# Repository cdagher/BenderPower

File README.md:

# Bender ARS Power Supply

This repo serves as the home for power supply designs for the Bender Autonomous Robotic Systems (ARS) project at Boise State University. It contains hardware source files including schematics and PCB layout, as well as all firmware source files.

This source is provided as is, with no warranty whatsoever. Feel free to use it in your own projects, so long as you follow the [licensing terms](LICENSE).

## Hardware

We wanted our hardware to be flexible, as requirements can change from year to year depending on the goals of our team, design of the robot, and the competition we are targeting. As a result of this, we determined that our power supply should be *modular*. I don't mean modular like a modular ATX power supply, I mean that we can put in almost any power source, and get almost any supply voltages and currents on the output. This is obviously a tall order, so we settled for an input voltage of 0~60 VDC, a switching capacity of 55 A, and having three replaceable power modules. These modules should be cold-swappable, and can be designed to output nearly any voltage and current within a set power budget. As a final piece, we gave the board three hot-swappable power inputs so that we can power it from multiple batteries or power supplies simultaneously if we want to.

Currently, our power supply is split into three parts as follows:

1. A switching board which handles up to three inputs which are digitally fused to handle things like over-current, under- and over-voltage conditions, brown-outs, over-temperature conditions. Just to name a few. There are also three slots for our replaceable power modules, and one bank of output terminals for motor drivers directly from the input voltage.

2. A series of power modules which fit into a "standard" socket. We made a standard for ourselves from off the shelf connectors such that the modules will sit flush with the switching board, in case we need to give them a heatsink.

3. A controller. Our digital fuses on the inputs and power modules communicate over PMBus, so we need a way of controlling and coordinating everything. As long as the controller fits the bolt pattern and shape specified, it will easily bolt on to the top of the switching board and connect to everything with a wire harness. The decision to break this out into a separate board also simplified design and routing on the switching baord, and allowed for it to be designed for a cheaper 2-layer manufacturing process.

Renderings of the various boards can be seen below.

**Switching Board**

Top view of the switching board

Bottom view of the switching board

**Power Module Examples**

TODO

**Controller**

Top view of the controller PCB

Bottom View of the controller PCB

Side view of the controller PCB

## Firmware
TODO

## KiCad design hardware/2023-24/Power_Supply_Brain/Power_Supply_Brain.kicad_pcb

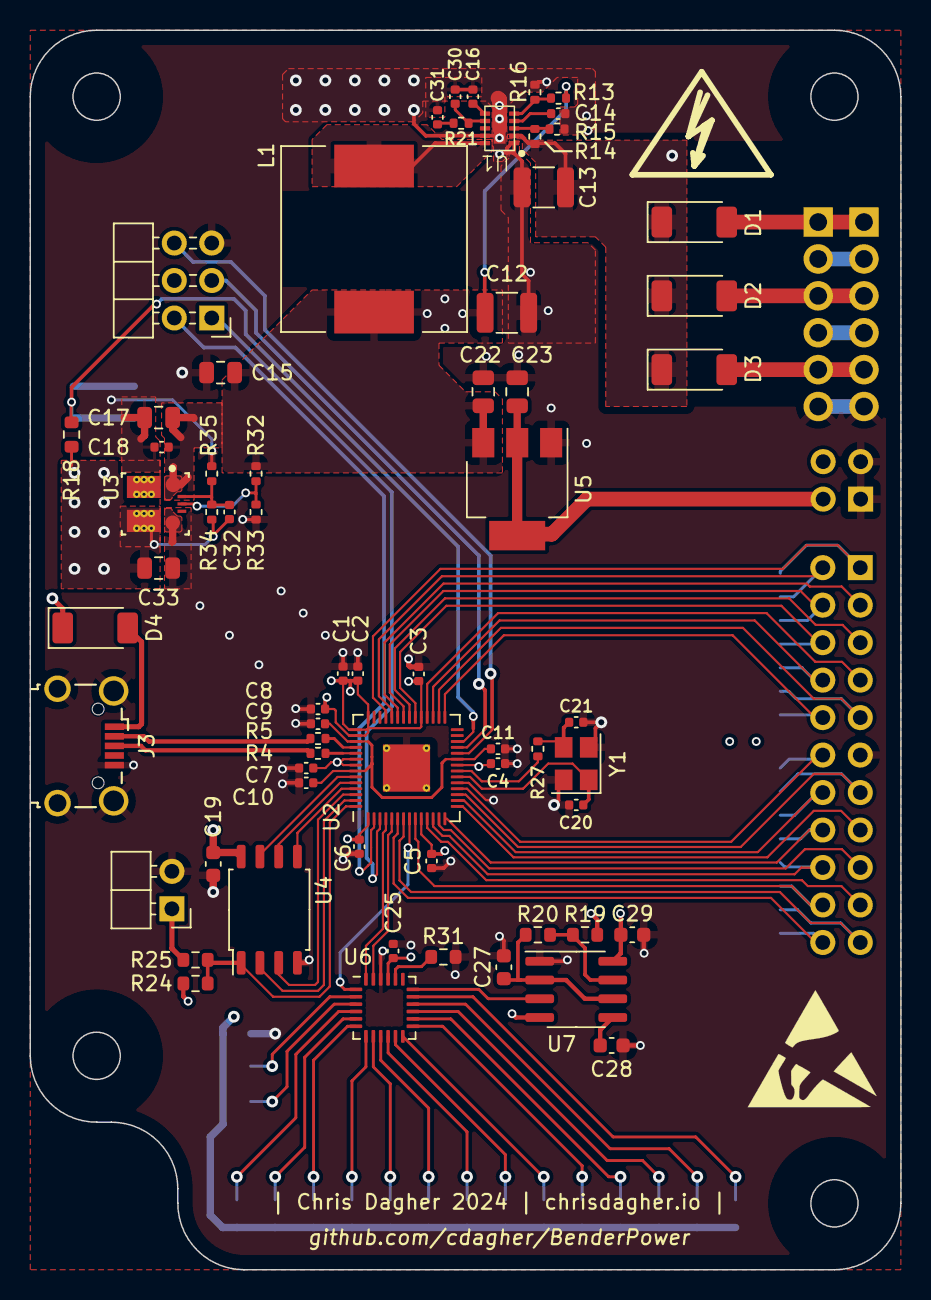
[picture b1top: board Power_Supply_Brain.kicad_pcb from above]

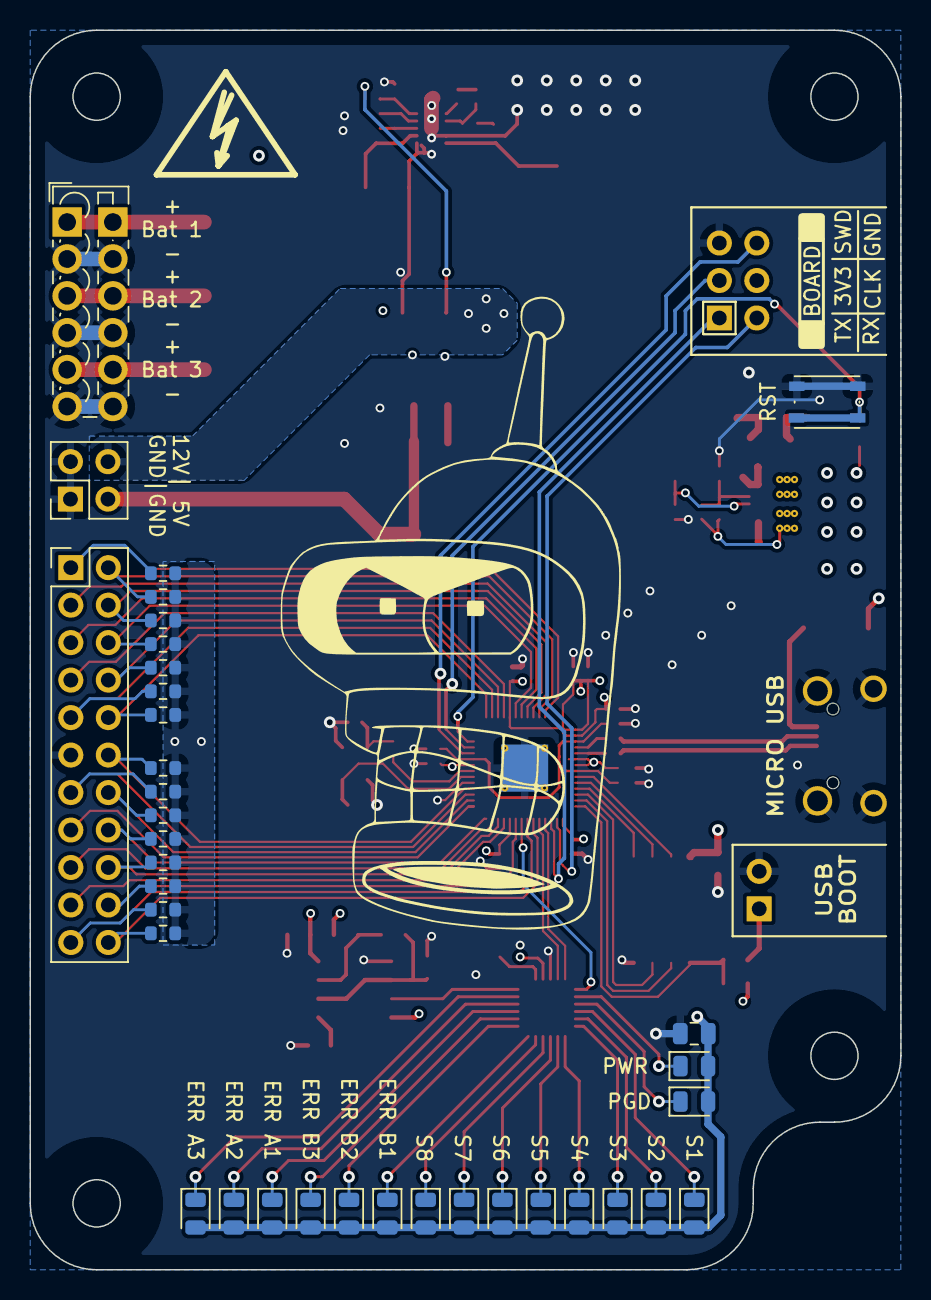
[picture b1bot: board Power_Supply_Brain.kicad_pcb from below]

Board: 4 copper layers, 59.0 x 84.0 mm, 101 parts (36 on the bottom side), 83 nets.

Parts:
C1, C2, C3, C4, C5, C6, C7, C10, C11, C18: 100n; C_0402_1005Metric
C8, C9, C14, C25: 1u; C_0402_1005Metric
C12: 10u; C_1210_3225Metric
C13: 2.2u; C_1210_3225Metric
C15, C17, C22, C23: 10u; C_0805_2012Metric
C16: 6800p; C_0402_1005Metric
C19: 100n; C_0603_1608Metric
C20, C21: 15p; C_0402_1005Metric
C26: 47u; C_0805_2012Metric
C27: 600p; C_0603_1608Metric
C28: DNP; C_0603_1608Metric
C29: 1u; C_0603_1608Metric
C30: 12p; C_0402_1005Metric
C31: 2200p; C_0402_1005Metric
C32: 22p; C_0402_1005Metric
C33: 22u; C_0805_2012Metric
D1, D2, D3, D4: PMEG10030ELPX; D_SOD-128
D5, D6, D7, D8, D9, D10, D11, D12, D13, D14, D15, D16, D17, D18, D19, D20: LED; LED_0805_2012Metric
J1: Conn_02x03_Odd_Even; PinHeader_2x03_P2.54mm_Horizontal
J2: Conn_02x02_Counter_Clockwise; PinHeader_2x02_P2.54mm_Vertical
J3: USB_B_Micro; USB_Micro-B_Wuerth_629105150521_CircularHoles
J4: Conn_01x02; PinHeader_1x02_P2.54mm_Horizontal
J5: Screw_Terminal_01x06; TerminalBlock_Phoenix_PTSM-0,5-6-2.5-V-THR_1x06_P2.50mm_Ver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
J6: Conn_02x11_Counter_Clockwise; PinHeader_2x11_P2.54mm_Vertical
L1: 47u; L_12x12mm_H6mm
R1, R2, R3, R6, R8, R9, R10, R11, R12, R18: 10k; R_0603_1608Metric
R4, R5: 27.4; R_0402_1005Metric
R7, R17, R22, R23, R26, R28: 100k; R_0603_1608Metric
R13: 174k; R_0402_1005Metric
R14: 3.3M; R_0402_1005Metric
R15: 453k; R_0402_1005Metric
R16: 14k; R_0402_1005Metric
R19: 220; R_0603_1608Metric
R20: 1.1k; R_0603_1608Metric
R21: 20k; R_0402_1005Metric
R24: DNP; R_0603_1608Metric
R25: 1k; R_0603_1608Metric
R27: 1k; R_0402_1005Metric
R31: 11k; R_0603_1608Metric
R32: 62k; R_0402_1005Metric
R33, R35: 30k; R_0402_1005Metric
R34: 135k; R_0402_1005Metric
SW1: SW_MEC_5G; SW_Push_1P1T_NO_Vertical_Wuerth_434133025816
U1: MAX17502G; TDFN
U2: RP2040; QFN-56-1EP_7x7mm_P0.4mm_EP3.2x3.2mm_ThermalVias
U3: TPSM861252RDXR; RDX0007A-MFG
U4: W25Q128JVS; SOIC-8_5.23x5.23mm_P1.27mm
U5: NCP1117-5.0_SOT223; SOT-223-3_TabPin2
U6: LED1642GWQTR; QFN-24-1EP_4x4mm_P0.5mm_EP2.15x2.15mm
U7: LMC555xM; SOIC-8_3.9x4.9mm_P1.27mm
Y1: ABLS-12.000MHZ-B4-T; Crystal_SMD_Abracon_ABM8G-4Pin_3.2x2.5mm

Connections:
+1V1: C9.1, C10.1, C11.1, U2.23 (DVDD), U2.45 (VREG_VOUT), U2.50 (DVDD)
+3V3: C1.1, C2.1, C3.1, C4.1, C5.1, C6.1, C7.1, C8.1, C19.1, C25.1, C26.1, C29.1, C32.1, C33.1, D5.2 (A), D6.2 (A), D7.2 (A), D8.2 (A), D9.2 (A), D10.2 (A), D11.2 (A), D12.2 (A), D13.2 (A), D14.2 (A), D15.2 (A), D16.2 (A), D17.2 (A), D18.2 (A), D19.2 (A), D20.2 (A), J1.4, R1.1, R2.2, R3.2, R6.2, R7.2, R8.1, R9.1, R10.1, R11.1, R12.1, R17.2, R18.1, R19.1, R22.2, R23.2, R24.1, R26.2, R28.2, R34.1, U2.1 (IOVDD), U2.10 (IOVDD), U2.22 (IOVDD), U2.33 (IOVDD), U2.42 (IOVDD), U2.43 (ADC_AVDD), U2.44 (VREG_IN), U2.48 (USB_VDD), U2.49 (IOVDD), U3.3 (VOUT), U3.11, U3.12, U3.13, U3.17, U3.18, U3.19, U4.8 (VCC), U6.21 (VDD), U7.4 (R), U7.8 (VCC)
+5V: C23.1, J2.3, U5.2 (VO)
+9V: C12.2 (-), C15.1, C17.1, C18.1, C22.1, J2.4, L1.2, R13.1, R32.1, U3.1 (VIN), U5.3 (VI)
/+12V_LX: L1.1, U1.10 (LX)
/LED Matrix/PWCLK: U6.18 (PWCLK), U7.3 (Q)
/LED Matrix/THR/TR: C27.1, R20.2, U7.2 (TR), U7.6 (THR)
/MCU_REG_IN: C13.2 (-), D1.1 (K), D2.1 (K), D3.1 (K), D4.1 (K), R14.1, U1.2 (VIN)
/QSPI_SCLK: U2.52 (QSPI_SCLK), U4.6 (CLK)
/QSPI_SD0: U2.53 (QSPI_SD0), U4.5 (DI(IO0))
/QSPI_SD1: U2.55 (QSPI_SD1), U4.2 (DO(IO1))
/QSPI_SD2: U2.54 (QSPI_SD2), U4.3 (IO2)
/QSPI_SD3: U2.51 (QSPI_SD3), U4.7 (IO3)
/QSPI_SS: R24.2, R25.1, U2.56 (QSPI_SS), U4.1 (~CS)
/SWCLK: J1.6, U2.24 (SWCLK)
/SWD: J1.3, U2.25 (SWD)
/UART0_RX: J1.1, U2.3 (GPIO1)
/UART0_TX: J1.2, U2.2 (GPIO0)
/USB_D_N: J3.2 (D-), R5.1
/USB_D_P: J3.3 (D+), R4.1
/XIN: C20.1, U2.20 (XIN), Y1.1
/XOUT: R27.1, U2.21 (XOUT)
/~USB_BOOT: J4.1, R25.2
ADC1_RDY: J6.10, R2.1, U2.29 (GPIO18)
ADC2_RDY: J6.9, R3.1, U2.30 (GPIO19)
ALRT_B1: J6.14, R8.2, U2.16 (GPIO13)
ALRT_B2: J6.13, R9.2, U2.17 (GPIO14)
ALRT_B3: J6.12, R10.2, U2.18 (GPIO15)
EN_AUX_1: J6.7, U2.32 (GPIO21)
EN_AUX_2: J6.5, U2.35 (GPIO23)
EN_AUX_3: J6.3, U2.37 (GPIO25)
EN_B1: J6.15, U2.15 (GPIO12)
EN_B2: J6.17, U2.13 (GPIO10)
EN_B3: J6.19, U2.11 (GPIO8)
GND: C1.2, C2.2, C3.2, C4.2, C5.2, C6.2, C7.2, C8.2, C9.2, C10.2, C11.2, C12.1 (+), C13.1 (+), C14.1 (+), C15.2, C16.1 (+), C17.2, C18.2, C19.2, C20.2, C21.2, C22.2, C23.2, C25.2, C26.2, C27.2, C28.1, C29.2, C30.2, C31.2, C33.2, J1.5, J2.1, J2.2, J3.5 (GND), J3.6 (Shield), J4.2, J5.2, J5.4, J5.6, J6.11, R15.2, R16.2, R31.1, R33.2, R35.2, SW1.2 (A), U1.1 (PGND), U1.9 (GND), U2.19 (TESTEN), U2.57 (GND), U3.4 (PGND), U4.4 (GND), U5.1 (GND), U6.22 (GND), U7.1 (GND), Y1.2 (3), Y1.4
I2C0_SCL: J6.21, R11.2, U2.7 (GPIO5)
I2C0_SDA: J6.22, R12.2, U2.6 (GPIO4)
I2C1_SCL: J6.1, R6.1, U2.39 (GPIO27_ADC1)
I2C1_SDA: J6.2, R1.2, U2.38 (GPIO26_ADC0)
LED_CLK: U2.4 (GPIO2), U6.24 (CLK)
LED_EN: U2.8 (GPIO6), U6.1 (LE)
LED_SDI: U2.5 (GPIO3), U6.23 (SDI)
unnamed: C14.2 (-), U1.4 (VCC)
unnamed: C16.2 (-), U1.6 (SS)
unnamed: C21.1, R27.2, Y1.3
unnamed: C31.1, R21.2
unnamed: D4.2 (A), J3.1 (VBUS)
unnamed: D5.1 (K), U6.2 (OUT0)
unnamed: D6.1 (K), U6.3 (OUT1)
unnamed: D7.1 (K), U6.4 (OUT2)
unnamed: D8.1 (K), U6.5 (OUT3)
unnamed: D9.1 (K), U6.6 (OUT4)
unnamed: D10.1 (K), U6.7 (OUT5)
unnamed: D11.1 (K), U6.8 (OUT6)
unnamed: D12.1 (K), U6.9 (OUT7)
unnamed: D13.1 (K), U6.10 (OUT8)
unnamed: D14.1 (K), U6.11 (OUT9)
unnamed: D15.1 (K), U6.12 (OUT10)
unnamed: D16.1 (K), U6.13 (OUT11)
unnamed: D17.1 (K), U6.14 (OUT12)
unnamed: D18.1 (K), U6.15 (OUT13)
unnamed: D19.1 (K), U6.16 (OUT14)
unnamed: D20.1 (K), U6.17 (OUT15)
unnamed: R14.2, R15.1, U1.3 (EN/UVLO)
unnamed: R13.2, R16.1, U1.5 (FB/VO)
unnamed: C30.1, R21.1, U1.7 (NC/COMP)
unnamed: R18.2, SW1.1 (A), U2.26 (RUN)
unnamed: R5.2, U2.46 (USB_DM)
unnamed: R4.2, U2.47 (USB_DP)
unnamed: R32.2, R33.1, U3.6 (EN)
unnamed: C32.2, R34.2, R35.1, U3.7 (FB)
unnamed: R31.2, U6.20 (R-EXT)
unnamed: C28.2, U7.5 (CV)
unnamed: R19.2, R20.1, U7.7 (DIS)
PGD_AUX1: J6.8, R23.1, U2.31 (GPIO20)
PGD_AUX2: J6.6, R26.1, U2.34 (GPIO22)
PGD_AUX3: J6.4, R28.1, U2.36 (GPIO24)
PGD_B1: J6.16, R7.1, U2.14 (GPIO11)
PGD_B2: J6.18, R17.1, U2.12 (GPIO9)
PGD_B3: J6.20, R22.1, U2.9 (GPIO7)
VIN_B1: D1.2 (A), J5.1
VIN_B2: D2.2 (A), J5.3
VIN_B3: D3.2 (A), J5.5

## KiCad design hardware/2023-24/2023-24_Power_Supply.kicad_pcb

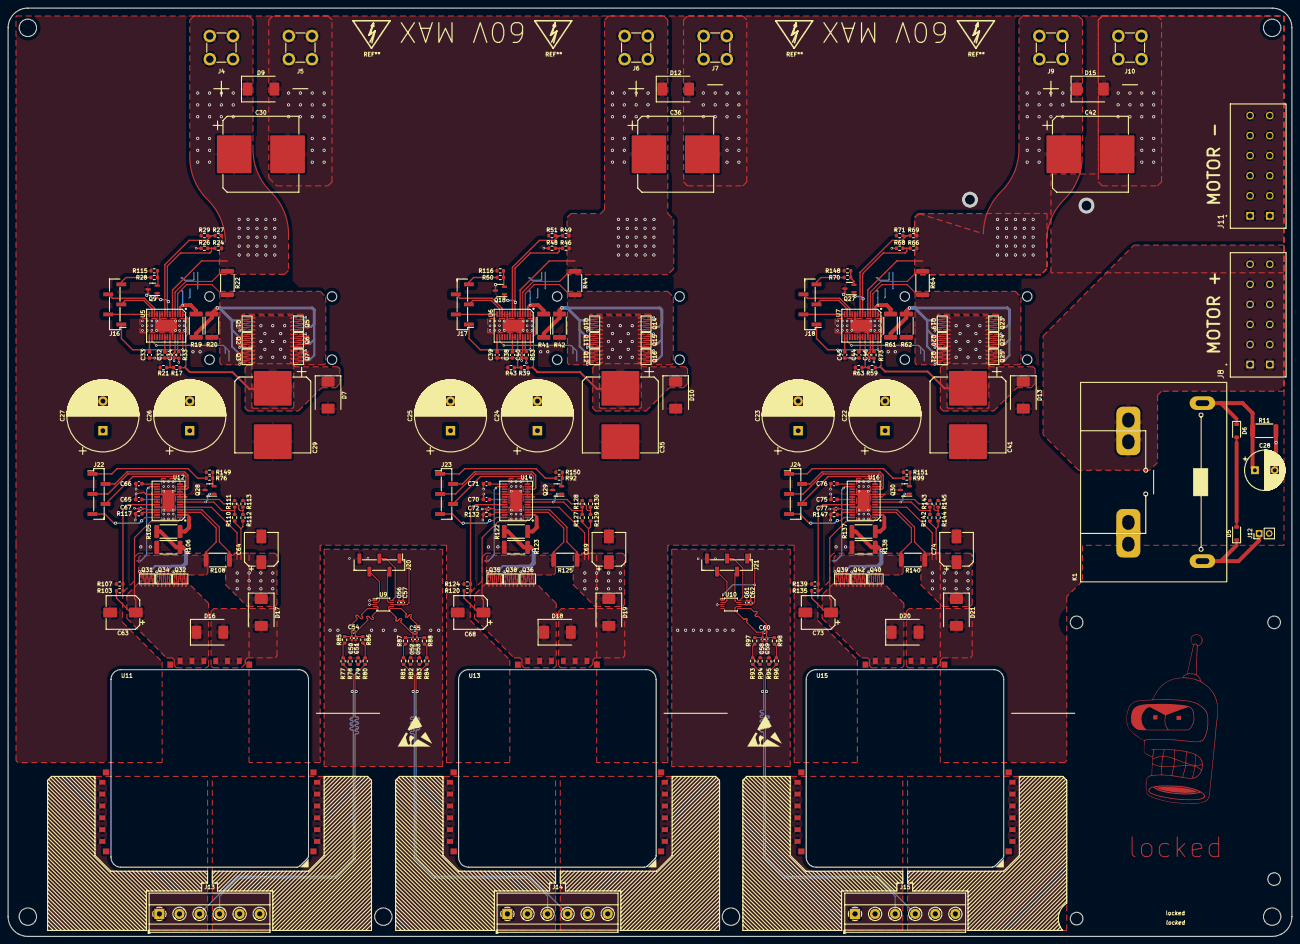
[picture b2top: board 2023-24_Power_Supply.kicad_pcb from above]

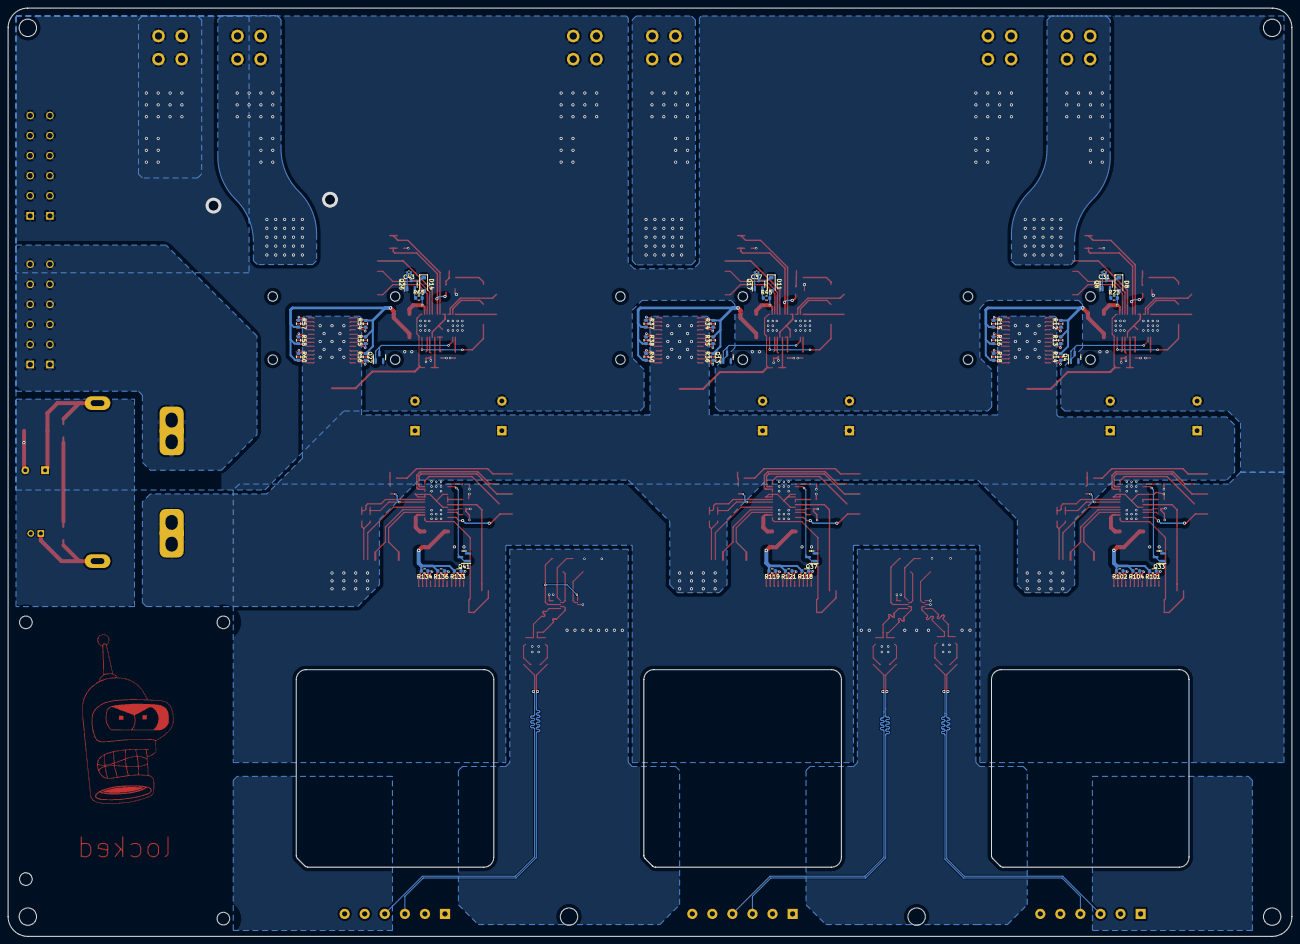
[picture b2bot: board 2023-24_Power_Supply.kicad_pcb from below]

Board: 2 copper layers, 325.0 x 235.0 mm, 265 parts (45 on the bottom side), 171 nets.

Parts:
C22, C23, C24, C25, C26, C27: 330u; CP_Radial_D18.0mm_P7.50mm
C28: 22u; CP_Radial_D10.0mm_P5.00mm
C29, C30, C35, C36, C41, C42: 220u; CP_Elec_18x17.5
C31, C37, C43: 30n; C_0402_1005Metric
C32, C33, C38, C39, C44, C45, C65, C66, C70, C71, C75, C76: 1u; C_0603_1608Metric
C34, C40, C46: 10n; C_0402_1005Metric
C50, C51, C52, C53, C58, C59: 50n; C_0402_1005Metric
C54, C55, C60: 5p; C_0402_1005Metric
C56, C61: 0.1u; C_0402_1005Metric
C57, C62: 1.0u; C_0402_1005Metric
C63, C64, C68, C69, C73, C74: 22u; CP_Elec_8x10
C67, C72, C77: 75n; C_0402_1005Metric
D5: 120V; D_SOD-123
D6: 36V; D_SOD-123
D7, D10, D13, D16, D18, D20: 80V; D_SMC
D8, D11, D14: 100V; D_SOD-123
D9, D12, D15, D17, D19, D21: 60V; D_SMC
J4, J5, J6, J7, J9, J10: Screw_Terminal_01x01; Wuerth_REDCUBE-THR_WP-THRSH_74651174_THR
J8, J11: TBL007A-508-06GY; CUI_TBL007A-508-06GY
J12: Conn_01x02; PinHeader_1x02_P2.54mm_Vertical
J13, J14, J15: Screw_Terminal_01x06; TerminalBlock_Phoenix_MKDS-1,5-6-5.08_1x06_P5.08mm_Horizont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
J16, J17, J18, J20, J21, J22, J23, J24: Conn_01x05_Pin; PinHeader_1x05_P2.54mm_Vertical_SMD_Pin1Left
K1: G9KB-1A-E DC12; Relay_SPST_Omron_G9KB
Q1, Q2, Q3, Q5, Q6, Q7, Q10, Q11, Q12, Q14, Q15, Q16, Q19, Q20, Q21, Q23, Q24, Q25, Q31, Q32, Q34, Q35, Q36, Q38, Q39, Q40, Q42: WLCSP-8
Q4, Q13, Q22, Q33, Q37, Q41: SOT-23
Q8, Q17, Q26: PNP; SOT-23-3
Q9, Q18, Q27, Q28, Q29, Q30: NMOS; SOT-23-3
R11: 68; R_2512_6332Metric
R12, R13, R14, R15, R16, R18, R34, R35, R36, R37, R38, R40, R54, R55, R56, R57, R58, R60: 180; R_0603_1608Metric
R17, R24, R39, R46, R59, R66, R77, R80, R81, R84, R93, R96, R103, R110, R120, R127, R135, R142: 100k; R_0603_1608Metric
R19, R41, R61, R105, R122, R137: 56; R_2512_6332Metric
R20, R42, R62, R106, R123, R138: 30; R_2512_6332Metric
R21, R43, R63, R107, R124, R139: 21.3k; R_0603_1608Metric
R22, R44, R64: 500u; R_2512_6332Metric
R23, R28, R45, R50, R65, R70, R76, R92, R99: 1k; R_0603_1608Metric
R26, R48, R68, R111, R128, R143: 33k; R_0603_1608Metric
R27, R49, R69, R112, R129, R144: 95k; R_0603_1608Metric
R29, R51, R71, R113, R130, R145: 3.9k; R_0603_1608Metric
R33, R53, R73: 45.3k; R_0603_1608Metric
R78, R79, R82, R83, R85, R86, R87, R88, R94, R95, R97, R98, R115, R116, R148, R149, R150, R151: 10k; R_0603_1608Metric
R101, R102, R104, R118, R119, R121, R133, R134, R136: 82.5; R_0603_1608Metric
R108, R125, R140: 1.5m; R_2512_6332Metric
R117, R132, R147: 28.2k; R_0603_1608Metric
U5, U6, U7, U12, U14, U16: LM5066; HTSSOP-28
U9, U10: ADS1015IDGS; TSSOP-10_3x3mm_P0.5mm
U11, U13, U15: 50x50_slot

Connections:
+5.5V: C56.1, C57.1, C61.1, C62.1, J20.1, J21.1, U9.8 (VDD), U10.1 (ADDR), U10.8 (VDD)
/Aux Outputs/Aux 1/DIODE: Q33.1 (B), Q33.3 (C), U12.16 (DIODE)
/Aux Outputs/Aux 1/GATE: R101.2, R102.2, R104.2, R105.2, R106.1
/Aux Outputs/Aux 1/GATE_OUT: R105.1, U12.2 (GATE)
/Aux Outputs/Aux 1/I2C_SCL: J22.3, U12.13 (SCLK)
/Aux Outputs/Aux 1/I2C_SDA: J22.2, U12.11 (SDAI), U12.12 (SDAO)
/Aux Outputs/Aux 1/REG_VIN: C63.1 (+), D16.1 (K), Q31.2 (S), Q32.2 (S), Q34.2 (S), R103.1, U11.1 (VIN_1), U11.2 (VIN_2), U11.3 (VIN_3), U12.1 (OUT)
/Aux Outputs/Aux 1/UVLO/EN: Q28.1 (G), R110.2, R111.2, U12.7 (UVLO/EN)
/Aux Outputs/Aux 1/VD: Q31.3 (D), Q32.3 (D), Q34.3 (D), R108.2, U12.3 (SENSE)
/Aux Outputs/Aux 1/VDD: C65.1 (+), U12.21 (VDD), U12.22 (CL)
/Aux Outputs/Aux 2/DIODE: Q37.1 (B), Q37.3 (C), U14.16 (DIODE)
/Aux Outputs/Aux 2/GATE: R118.2, R119.2, R121.2, R122.2, R123.1
/Aux Outputs/Aux 2/GATE_OUT: R122.1, U14.2 (GATE)
/Aux Outputs/Aux 2/I2C_SCL: J23.3, U14.13 (SCLK)
/Aux Outputs/Aux 2/I2C_SDA: J23.2, U14.11 (SDAI), U14.12 (SDAO)
/Aux Outputs/Aux 2/REG_VIN: C68.1 (+), D18.1 (K), Q35.2 (S), Q36.2 (S), Q38.2 (S), R120.1, U13.1 (VIN_1), U13.2 (VIN_2), U13.3 (VIN_3), U14.1 (OUT)
/Aux Outputs/Aux 2/UVLO/EN: Q29.1 (G), R127.2, R128.2, U14.7 (UVLO/EN)
/Aux Outputs/Aux 2/VD: Q35.3 (D), Q36.3 (D), Q38.3 (D), R125.2, U14.3 (SENSE)
/Aux Outputs/Aux 2/VDD: C70.1 (+), U14.21 (VDD), U14.22 (CL)
/Aux Outputs/Aux 3/DIODE: Q41.1 (B), Q41.3 (C), U16.16 (DIODE)
/Aux Outputs/Aux 3/GATE: R133.2, R134.2, R136.2, R137.2, R138.1
/Aux Outputs/Aux 3/GATE_OUT: R137.1, U16.2 (GATE)
/Aux Outputs/Aux 3/I2C_SCL: J24.3, U16.13 (SCLK)
/Aux Outputs/Aux 3/I2C_SDA: J24.2, U16.11 (SDAI), U16.12 (SDAO)
/Aux Outputs/Aux 3/REG_VIN: C73.1 (+), D20.1 (K), Q39.2 (S), Q40.2 (S), Q42.2 (S), R135.1, U15.1 (VIN_1), U15.2 (VIN_2), U15.3 (VIN_3), U16.1 (OUT)
/Aux Outputs/Aux 3/UVLO/EN: Q30.1 (G), R142.2, R143.2, U16.7 (UVLO/EN)
/Aux Outputs/Aux 3/VD: Q39.3 (D), Q40.3 (D), Q42.3 (D), R140.2, U16.3 (SENSE)
/Aux Outputs/Aux 3/VDD: C75.1 (+), U16.20 (ADR0), U16.21 (VDD), U16.22 (CL)
/Aux Outputs/VOUT_AUX1_+: J13.1, J13.2, J13.3, R77.1, U11.7 (VOUT_1), U11.8 (VOUT_2), U11.9 (VOUT_3), U11.10 (VOUT_4), U11.11 (VOUT_5), U11.12 (VOUT_6)
/Aux Outputs/VOUT_AUX1_-: J13.4, J13.5, J13.6, R80.2, U11.13 (PGND_1), U11.14 (PGND_2), U11.15 (PGND_3), U11.16 (PGND_4), U11.17 (PGND_5), U11.18 (PGND_6)
/Aux Outputs/VOUT_AUX2_+: J14.1, J14.2, J14.3, R81.1, U13.7 (VOUT_1), U13.8 (VOUT_2), U13.9 (VOUT_3), U13.10 (VOUT_4), U13.11 (VOUT_5), U13.12 (VOUT_6)
/Aux Outputs/VOUT_AUX2_-: J14.4, J14.5, J14.6, R84.2, U13.13 (PGND_1), U13.14 (PGND_2), U13.15 (PGND_3), U13.16 (PGND_4), U13.17 (PGND_5), U13.18 (PGND_6)
/Aux Outputs/VOUT_AUX3_+: J15.1, J15.2, J15.3, R93.1, U15.7 (VOUT_1), U15.8 (VOUT_2), U15.9 (VOUT_3), U15.10 (VOUT_4), U15.11 (VOUT_5), U15.12 (VOUT_6)
/Aux Outputs/VOUT_AUX3_-: J15.4, J15.5, J15.6, R96.2, U15.13 (PGND_1), U15.14 (PGND_2), U15.15 (PGND_3), U15.16 (PGND_4), U15.17 (PGND_5), U15.18 (PGND_6)
/Battery Switching/Battery 1/DIODE: Q4.1 (B), Q4.3 (C), U5.16 (DIODE)
/Battery Switching/Battery 1/GATE: R12.2, R13.2, R14.2, R15.2, R16.2, R18.2, R19.2, R20.1
/Battery Switching/Battery 1/GATE_OUT: D8.2 (A+), R19.1, R23.2, U5.2 (GATE)
/Battery Switching/Battery 1/I2C_SCL: J16.3, U5.13 (SCLK)
/Battery Switching/Battery 1/I2C_SDA: J16.4, U5.11 (SDAI), U5.12 (SDAO)
/Battery Switching/Battery 1/UVLO/EN: Q9.1 (G), R24.2, R26.2, U5.7 (UVLO/EN)
/Battery Switching/Battery 1/VD: Q1.3 (D), Q2.3 (D), Q3.3 (D), Q5.3 (D), Q6.3 (D), Q7.3 (D), R22.2, U5.3 (SENSE)
/Battery Switching/Battery 1/VDD: C32.1 (+), U5.21 (VDD), U5.22 (CL)
/Battery Switching/Battery 2/DIODE: Q13.1 (B), Q13.3 (C), U6.16 (DIODE)
/Battery Switching/Battery 2/GATE: R34.2, R35.2, R36.2, R37.2, R38.2, R40.2, R41.2, R42.1
/Battery Switching/Battery 2/GATE_OUT: D11.2 (A+), R41.1, R45.2, U6.2 (GATE)
/Battery Switching/Battery 2/I2C_SCL: J17.3, U6.13 (SCLK)
/Battery Switching/Battery 2/I2C_SDA: J17.4, U6.11 (SDAI), U6.12 (SDAO)
/Battery Switching/Battery 2/UVLO/EN: Q18.1 (G), R46.2, R48.2, U6.7 (UVLO/EN)
/Battery Switching/Battery 2/VD: Q10.3 (D), Q11.3 (D), Q12.3 (D), Q14.3 (D), Q15.3 (D), Q16.3 (D), R44.2, U6.3 (SENSE)
/Battery Switching/Battery 2/VDD: C38.1 (+), U6.21 (VDD), U6.22 (CL)
/Battery Switching/Battery 3/DIODE: Q22.1 (B), Q22.3 (C), U7.16 (DIODE)
/Battery Switching/Battery 3/GATE: R54.2, R55.2, R56.2, R57.2, R58.2, R60.2, R61.2, R62.1
/Battery Switching/Battery 3/GATE_OUT: D14.2 (A+), R61.1, R65.2, U7.2 (GATE)
/Battery Switching/Battery 3/I2C_SCL: J18.3, U7.13 (SCLK)
/Battery Switching/Battery 3/I2C_SDA: J18.4, U7.11 (SDAI), U7.12 (SDAO)
/Battery Switching/Battery 3/UVLO/EN: Q27.1 (G), R66.2, R68.2, U7.7 (UVLO/EN)
/Battery Switching/Battery 3/VD: Q19.3 (D), Q20.3 (D), Q21.3 (D), Q23.3 (D), Q24.3 (D), Q25.3 (D), R64.2, U7.3 (SENSE)
/Battery Switching/Battery 3/VDD: C44.1 (+), U7.20 (ADR0), U7.21 (VDD), U7.22 (CL)
ADC1_RDY: J20.4, U9.2 (ALERT/RDY)
ADC2_RDY: J21.4, U10.2 (ALERT/RDY)
ALRT_AUX1: J22.4, U12.14 (SMBA)
ALRT_AUX2: J23.4, U14.14 (SMBA)
ALRT_AUX3: J24.4, U16.14 (SMBA)
ALRT_B1: J16.2, U5.14 (SMBA)
ALRT_B2: J17.2, U6.14 (SMBA)
ALRT_B3: J18.2, U7.14 (SMBA)
EN_AUX_1: J22.1, R76.1
EN_AUX_2: J23.1, R92.1
EN_AUX_3: J24.1, R99.1
EN_B1: J16.5, R28.1
EN_B2: J17.5, R50.1
EN_B3: J18.5, R70.1
GND: C22.2 (-), C23.2 (-), C24.2 (-), C25.2 (-), C26.2 (-), C27.2 (-), C29.2 (-), C30.2 (-), C31.2 (-), C32.2 (-), C33.2 (-), C34.2 (-), C35.2 (-), C36.2 (-), C37.2 (-), C38.2 (-), C39.2 (-), C40.2 (-), C41.2 (-), C42.2 (-), C43.2 (-), C44.2 (-), C45.2 (-), C46.2 (-), C50.1, C51.1, C52.1, C53.1, C56.2, C57.2, C58.1, C59.1, C61.2, C62.2, C63.2 (-), C64.2 (-), C65.2 (-), C66.2 (-), C67.2 (-), C68.2 (-), C69.2 (-), C70.2 (-), C71.2 (-), C72.2 (-), C73.2 (-), C74.2 (-), C75.2 (-), C76.2 (-), C77.2 (-), D7.2 (A), D9.2 (A), D10.2 (A), D12.2 (A), D13.2 (A), D15.2 (A), D16.2 (A), D17.2 (A), D18.2 (A), D19.2 (A), D20.2 (A), D21.2 (A), J5.1, J7.1, J10.1, J11.1_A (1), J11.1_B (1__1), J11.2_A (2), J11.2_B (2__1), J11.3_A (3), J11.3_B (3__1), J11.4_A (4), J11.4_B (4__1), J11.5_A (5), J11.5_B (5__1), J11.6_A (6), J11.6_B (6__1), J20.5, J21.5, Q4.2 (E), Q8.1 (B), Q9.3 (D), Q13.2 (E), Q17.1 (B), Q18.3 (D), Q22.2 (E), Q26.1 (B), Q27.3 (D), Q28.3 (D), Q29.3 (D), Q30.3 (D), Q33.2 (E), Q37.2 (E), Q41.2 (E), R20.2, R21.2, R26.1, R29.1, R33.1, R42.2, R43.2, R48.1, R51.1, R53.1, R62.2, R63.2, R68.1, R71.1, R73.1, R78.2, R79.1, R82.2, R83.1, R94.2, R95.1, R106.2, R107.2, R111.1, R113.1, R115.2, R116.2, R117.1, R123.2, R124.2, R128.1, R130.1, R132.1, R138.2, R139.2, R143.1, R145.1, R147.1, R148.2, R149.2, R150.2, R151.2, U5.9 (AGND), U5.10 (GND), U5.24 (RETRY), U6.9 (AGND), U6.10 (GND), U6.20 (ADR0), U6.24 (RETRY), U7.9 (AGND), U7.10 (GND), U7.24 (RETRY), U9.1 (ADDR), U9.3 (GND), U10.3 (GND), U11.4 (GND_1), U11.5 (GND_2), U11.6 (GND_3), U12.9 (AGND), U12.10 (GND), U12.19 (ADR1), U12.24 (RETRY), U13.4 (GND_1), U13.5 (GND_2), U13.6 (GND_3), U14.9 (AGND), U14.10 (GND), U14.19 (ADR1), U14.20 (ADR0), U14.24 (RETRY), U15.4 (GND_1), U15.5 (GND_2), U15.6 (GND_3), U16.9 (AGND), U16.10 (GND), U16.19 (ADR1), U16.24 (RETRY)
GND2: C28.2, J12.2, R11.2
I2C1_SCL: J20.3, J21.3, U9.10 (SCL), U10.10 (SCL)
I2C1_SDA: J20.2, J21.2, U9.9 (SDA), U10.9 (SDA)
unnamed: C31.1 (+), D8.1 (K-), Q8.3 (C)
unnamed: C33.1 (+), U5.15 (VREF)
unnamed: C34.1 (+), U5.25 (TIMER)
unnamed: C37.1 (+), D11.1 (K-), Q17.3 (C)
unnamed: C39.1 (+), U6.15 (VREF)
unnamed: C40.1 (+), U6.25 (TIMER)
unnamed: C43.1 (+), D14.1 (K-), Q26.3 (C)
unnamed: C45.1 (+), U7.15 (VREF)
unnamed: C46.1 (+), U7.25 (TIMER)
unnamed: C66.1 (+), U12.15 (VREF)
unnamed: C67.1 (+), U12.25 (TIMER)
unnamed: C71.1 (+), U14.15 (VREF)
unnamed: C72.1 (+), U14.25 (TIMER)
unnamed: C76.1 (+), U16.15 (VREF)
unnamed: C77.1 (+), U16.25 (TIMER)
unnamed: D5.2 (A+), D6.2 (A)
unnamed: C28.1, D6.1 (K), K1.2 (COIL_2), R11.1
unnamed: Q1.1 (G), R12.1
unnamed: Q2.1 (G), R13.1
unnamed: Q3.1 (G), R14.1
unnamed: Q5.1 (G), R15.1
unnamed: Q6.1 (G), R16.1
unnamed: Q7.1 (G), R18.1
unnamed: Q8.2 (E), R23.1
unnamed: Q9.2 (S), R28.2, R115.1
unnamed: Q10.1 (G), R34.1
unnamed: Q11.1 (G), R35.1
unnamed: Q12.1 (G), R36.1
unnamed: Q14.1 (G), R37.1
unnamed: Q15.1 (G), R38.1
unnamed: Q16.1 (G), R40.1
unnamed: Q17.2 (E), R45.1
unnamed: Q18.2 (S), R50.2, R116.1
unnamed: Q19.1 (G), R54.1
unnamed: Q20.1 (G), R55.1
unnamed: Q21.1 (G), R56.1
unnamed: Q23.1 (G), R57.1
unnamed: Q24.1 (G), R58.1
unnamed: Q25.1 (G), R60.1
unnamed: Q26.2 (E), R65.1
unnamed: Q27.2 (S), R70.2, R148.1
unnamed: Q28.2 (S), R76.2, R149.1
unnamed: Q29.2 (S), R92.2, R150.1
unnamed: Q30.2 (S), R99.2, R151.1
unnamed: Q31.1 (G), R101.1
unnamed: Q32.1 (G), R102.1
unnamed: Q34.1 (G), R104.1
unnamed: Q35.1 (G), R118.1
unnamed: Q36.1 (G), R119.1
unnamed: Q38.1 (G), R121.1
unnamed: Q39.1 (G), R133.1
unnamed: Q40.1 (G), R134.1
unnamed: Q42.1 (G), R136.1
unnamed: R77.2, R78.1, R85.2
unnamed: R79.2, R80.1, R86.2
unnamed: R81.2, R82.1, R87.2
unnamed: R83.2, R84.1, R88.2
unnamed: R93.2, R94.1, R97.2
unnamed: R95.2, R96.1, R98.2
unnamed: R17.2, R21.1, U5.23 (FB)
unnamed: R27.1, R29.2, U5.8 (OVLO)
unnamed: R33.2, U5.26 (PWR)
unnamed: R39.2, R43.1, U6.23 (FB)
unnamed: R49.1, R51.2, U6.8 (OVLO)
unnamed: R53.2, U6.26 (PWR)
unnamed: R59.2, R63.1, U7.23 (FB)
unnamed: R69.1, R71.2, U7.8 (OVLO)
unnamed: R73.2, U7.26 (PWR)
unnamed: C51.2, C54.2, R86.1, U9.4 (AIN0)
unnamed: C50.2, C54.1, R85.1, U9.5 (AIN1)
unnamed: C53.2, C55.2, R88.1, U9.6 (AIN2)
unnamed: C52.2, C55.1, R87.1, U9.7 (AIN3)
unnamed: C59.2, C60.2, R98.1, U10.6 (AIN2)
unnamed: C58.2, C60.1, R97.1, U10.7 (AIN3)
unnamed: R103.2, R107.1, U12.23 (FB)
unnamed: R112.1, R113.2, U12.8 (OVLO)
unnamed: R117.2, U12.26 (PWR)
unnamed: R120.2, R124.1, U14.23 (FB)
unnamed: R129.1, R130.2, U14.8 (OVLO)
unnamed: R132.2, U14.26 (PWR)
unnamed: R135.2, R139.1, U16.23 (FB)
unnamed: R144.1, R145.2, U16.8 (OVLO)
unnamed: R147.2, U16.26 (PWR)
PGD_AUX1: J22.5, U12.28 (PGD)
PGD_AUX2: J23.5, U14.28 (PGD)
PGD_AUX3: J24.5, U16.28 (PGD)
PGD_B1: J16.1, U5.28 (PGD)
PGD_B2: J17.1, U6.28 (PGD)
PGD_B3: J18.1, U7.28 (PGD)
RELAY_EN: D5.1 (K-), J12.1, K1.1 (COIL_1)
VIN_B1: C30.1 (+), D9.1 (K), J4.1, R22.1, R24.1, R27.2, U5.4 (VIN_K), U5.5 (VIN)
VIN_B2: C36.1 (+), D12.1 (K), J6.1, R44.1, R46.1, R49.2, U6.4 (VIN_K), U6.5 (VIN)
VIN_B3: C42.1 (+), D15.1 (K), J9.1, R64.1, R66.1, R69.2, U7.4 (VIN_K), U7.5 (VIN)
V_MOT: J8.1_A (1), J8.1_B (1__1), J8.2_A (2), J8.2_B (2__1), J8.3_A (3), J8.3_B (3__1), J8.4_A (4), J8.4_B (4__1), J8.5_A (5), J8.5_B (5__1), J8.6_A (6), J8.6_B (6__1), K1.4 (CONTACT_2)
V_SYS: C22.1 (+), C23.1 (+), C24.1 (+), C25.1 (+), C26.1 (+), C27.1 (+), C29.1 (+), C35.1 (+), C41.1 (+), C64.1 (+), C69.1 (+), C74.1 (+), D7.1 (K), D10.1 (K), D13.1 (K), D17.1 (K), D19.1 (K), D21.1 (K), K1.3 (CONTACT_1), Q1.2 (S), Q2.2 (S), Q3.2 (S), Q5.2 (S), Q6.2 (S), Q7.2 (S), Q10.2 (S), Q11.2 (S), Q12.2 (S), Q14.2 (S), Q15.2 (S), Q16.2 (S), Q19.2 (S), Q20.2 (S), Q21.2 (S), Q23.2 (S), Q24.2 (S), Q25.2 (S), R17.1, R39.1, R59.1, R108.1, R110.1, R112.2, R125.1, R127.1, R129.2, R140.1, R142.1, R144.2, U5.1 (OUT), U6.1 (OUT), U7.1 (OUT), U12.4 (VIN_K), U12.5 (VIN), U14.4 (VIN_K), U14.5 (VIN), U16.4 (VIN_K), U16.5 (VIN)

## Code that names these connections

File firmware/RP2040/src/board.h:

// Board configuration for RP2040

#ifndef BOARD_H
#define BOARD_H

#include "pico/stdlib.h"
#include "hardware/gpio.h"

#define BOARD_BENDER_BRAIN

// General pin configurations
#define UART_0_TX 0
#define UART_0_PIN_MODE GPIO_FUNC_UART
#define UART_0_RX 1
#define UART_0_PIN_MODE GPIO_FUNC_UART

#define I2C0_SDA 4
#define I2C0_PIN_MODE GPIO_FUNC_I2C
#define I2C0_SCL 5
#define I2C0_PIN_MODE GPIO_FUNC_I2C

#define I2C1_SDA 26
#define I2C1_PIN_MODE GPIO_FUNC_I2C
#define I2C1_SCL 27
#define I2C1_PIN_MODE GPIO_FUNC_I2C

// LED Driver pins
/*
LED Deiver is the LED1642GW from ST Microelectronics https://www.st.com/resource/en/datasheet/led1642gw.pdf

Note that the SDO pin is not used in this configuration, so there is no feedback
from the LED driver to the RP2040.
*/
#define LED_CLK 2
#define LED_CLK_MODE GPIO_FUNC_SIO
#define LED_SDI 3
#define LED_SDI_MODE GPIO_FUNC_SIO
#define LED_LEN  6
#define LED_LEN_MODE GPIO_FUNC_SIO

/* Battery Inputs 
Batteries are controlled using LM5066I ICs from Texas Instruments.

Batteries should use I2C0 for communication with the RP2040.
*/

#define BATTERY_1_ADDR 0x40
#define BATTERY_1_EN 12
#define BATTERY_1_EN_PIN_MODE GPIO_FUNC_SIO
#define BATTERY_1_ALERT 13
#define BATTERY_1_ALERT_PIN_MODE GPIO_FUNC_SIO
#define BATTERY_1_PGD 11
#define BATTERY_1_PGD_PIN_MODE GPIO_FUNC_SIO

#define BATTERY_2_ADDR 0x41
#define BATTERY_2_EN 10
#define BATTERY_2_EN_PIN_MODE GPIO_FUNC_SIO
#define BATTERY_2_ALERT 14
#define BATTERY_2_ALERT_PIN_MODE GPIO_FUNC_SIO
#define BATTERY_2_PGD 9
#define BATTERY_2_PGD_PIN_MODE GPIO_FUNC_SIO

#define BATTERY_3_ADDR 0x42
#define BATTERY_3_EN 8
#define BATTERY_3_EN_PIN_MODE GPIO_FUNC_SIO
#define BATTERY_3_ALERT 15
#define BATTERY_3_ALERT_PIN_MODE GPIO_FUNC_SIO
#define BATTERY_3_PGD 7
#define BATTERY_3_PGD_PIN_MODE GPIO_FUNC_SIO

/* ADC Inputs
ADCs are used to read the voltage output from the baord's auxiliary outputs.
The ADCs used are 2x ADS1015 from Texas Instruments

ADCs should use I2C1 for communication with the RP2040.
*/

#define ADC_1_ADDR 0x48
#define ADC_1_RDY 18
#define ADC_1_RDY_PIN_MODE GPIO_FUNC_SIO

#define ADC_2_ADDR 0x49
#define ADC_2_RDY 19
#define ADC_2_RDY_PIN_MODE GPIO_FUNC_SIO

/* Auxiliary Outputs
Auxiliary outputs are controlled using LM5066I ICs from Texas Instruments.
Note that due to a shortage of GPIO pins and board space, the auxiliary outputs
have no alert pins. This means that in order to detect a fault, the RP2040 must
poll the auxiliary outputs.

Auxiliary outputs should use I2C1 for communication with the RP2040.
*/

#define AUX_DUMMY_ALERT 16
#define AUX_DUMMY_ALERT_PIN_MODE GPIO_FUNC_SIO

#define AUX_1_ADDR 0x43
#define AUX_1_EN 21
#define AUX_1_EN_PIN_MODE GPIO_FUNC_SIO
// #define AUX_1_ALERT 20
#define AUX_1_PGD 20
#define AUX_1_PGD_PIN_MODE GPIO_FUNC_SIO

#define AUX_2_ADDR 0x44
#define AUX_2_EN 23
#define AUX_2_EN_PIN_MODE GPIO_FUNC_SIO
// #define AUX_2_ALERT 22
#define AUX_2_PGD 22
#define AUX_2_PGD_PIN_MODE GPIO_FUNC_SIO

#define AUX_3_ADDR 0x45
#define AUX_3_EN 25
#define AUX_3_EN_PIN_MODE GPIO_FUNC_SIO
// #define AUX_3_ALERT 24
#define AUX_3_PGD 24
#define AUX_3_PGD_PIN_MODE GPIO_FUNC_SIO

#endif // BOARD_H

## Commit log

2023-11-30 MCU and Battery inputs initial design
2023-12-17 regulator slot libraries
2023-12-17 connector datasheets
2024-01-18 Pushing for design review
2024-07-12 Hardware ready for design review
2024-08-13 update hardware gitignore
2024-08-13 design updated post review
2024-08-13 Set up firmware files
2024-08-13 Some initial code, but it's a starting point.
2024-08-13 Add README
2024-08-14 Improved crystal layout. Re-ordered debug connector. Fixed silkscreen.
2025-04-02 Pushing for pre-production review
2025-04-02 Updated BoM for supply and brain
2025-05-05 Added LED1642GW lib
2025-05-05 cmake configuration
2025-05-05 ADS1015 setup
2025-05-05 Adding board configuration
2025-05-05 configuring cmake
2025-05-05 add board header interface
2025-05-05 Updated to include SPI
2025-05-05 Updated board file
2025-05-05 partial work on ads1015
2025-05-05 ads1015 lib
2025-05-05 fix cmake issues
2025-05-05 Initial header for LM5066
2025-05-05 command macros for lm5066
2025-05-07 foward progress
2025-05-07 lm5066 lib
2025-05-07 fix read/write stuff
2025-05-08 Added sense resistor argument to constructor. Updated telemetry logic to use sense resistor value.
2025-05-11 fix syntax and cmake bugs
2025-05-11 add shell class
2025-05-11 Update for compatibility with board design
2025-05-11 Add device addresses
2025-05-11 Initial setup code
2025-05-11 Update cmakelists and fixes in main
2025-05-11 Working LED driver library
2025-05-11 LED driver working
2025-05-13 add basic shell functions
2025-05-13 getting main to work
2025-05-13 fixing qeftser's mistakes
